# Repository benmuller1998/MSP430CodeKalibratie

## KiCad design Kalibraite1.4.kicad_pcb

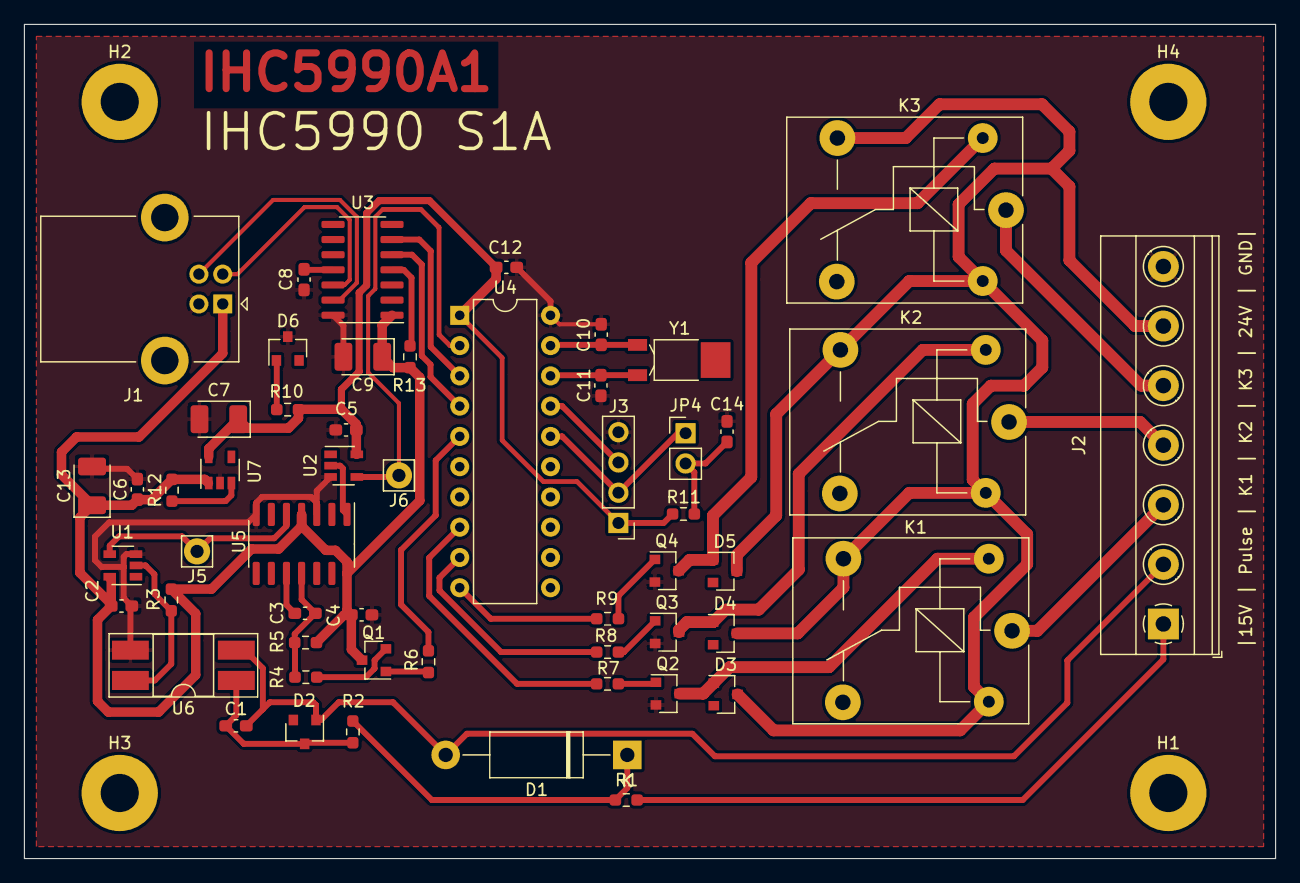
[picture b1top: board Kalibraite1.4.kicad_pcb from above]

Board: 2 copper layers, 105.0 x 70.0 mm, 58 parts (0 on the bottom side), 42 nets.

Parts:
C1: 100pF; C_0603_1608Metric_Pad1.08x0.95mm_HandSolder
C2, C4, C5, C6, C8, C12: 100nF; C_0603_1608Metric_Pad1.08x0.95mm_HandSolder
C3: 68nF; C_0603_1608Metric_Pad1.08x0.95mm_HandSolder
C7, C9, C13: 10uF; CP_EIA-3528-12_Kemet-T_Pad1.50x2.35mm_HandSolder
C10, C11: 15pF; C_0603_1608Metric_Pad1.08x0.95mm_HandSolder
C14: 10n; C_0603_1608Metric_Pad1.08x0.95mm_HandSolder
D1: P6KE13CA; D_DO-15_P15.24mm_Horizontal
D2, D3, D4, D5: 1N4148; D_SOT-23_ANK
D6: LED; D_SOT-23_ANK
H1, H2, H3, H4: MountingHole; MountingHole_3.2mm_M3_Pad
J1: USB_B; USB_B_Lumberg_2411_02_Horizontal
J2: Conn_01x07_Female; TerminalBlock_Phoenix_MKDS-1,5-7_1x07_P5.00mm_Horizontal
J3: Pin header; PinHeader_1x04_P2.54mm_Vertical
J5, J6: Header; Pin_D1.1mm_L8.5mm_W2.5mm_FlatFork
JP4: Jumper_2_Open; PinHeader_1x02_P2.54mm_Vertical
K1, K2, K3: G5LE; Relay_SPDT_SANYOU_SRD_Series_Form_C
Q1: BSN20; SOT-23
Q2, Q3, Q4: BC847; SOT-23
R1: 1K5; R_0603_1608Metric_Pad0.98x0.95mm_HandSolder
R2: 1K2; R_0603_1608Metric_Pad0.98x0.95mm_HandSolder
R3, R7, R8: 4K7; R_0603_1608Metric_Pad0.98x0.95mm_HandSolder
R4: 470; R_0603_1608Metric_Pad0.98x0.95mm_HandSolder
R5: 5K6; R_0603_1608Metric_Pad0.98x0.95mm_HandSolder
R6: 10K; R_0603_1608Metric_Pad0.98x0.95mm_HandSolder
R9, R12: 4k7; R_0603_1608Metric_Pad0.98x0.95mm_HandSolder
R10: 270; R_0603_1608Metric_Pad0.98x0.95mm_HandSolder
R11: 47k; R_0603_1608Metric_Pad0.98x0.95mm_HandSolder
R13: 1K; R_0603_1608Metric_Pad0.98x0.95mm_HandSolder
U1, U2: 74VHC1G14; SOT-23-5
U3: MCP2221AxP; SOIC-14_3.9x8.7mm_P1.27mm
U4: MSP430G2553IN20; DIP-20_W7.62mm
U5: 74121; SOIC-14_3.9x8.7mm_P1.27mm
U6: SFH617A-1; DIP-4_W8.89mm_SMDSocket_LongPads
U7: MIC5317-3.3YM5-TR; SOT-23-5
Y1: 32.768kHz; Crystal_SMD_MicroCrystal_MS1V-T1K

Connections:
+3V3: C5.1, C7.1, C12.2, J3.1, R10.1, R11.1, U2.5, U4.1, U7.5
+5V: C2.2, C4.1, C6.1, C9.1, C13.1, J1.1, Q1.3, R3.1, R5.1, R12.2, R13.2, U1.5, U3.1, U5.4, U5.14, U7.1
+24V: D3.1, D4.1, D5.1, J2.6, K1.3, K1.5, K2.3, K2.5, K3.3, K3.5
GND: C2.1, C4.2, C5.2, C6.2, C7.2, C8.1, C9.2, C10.1, C11.1, C12.1, C13.2, C14.2, D6.1, J1.4, J2.7, J3.4, Q2.2, Q3.2, Q4.2, U1.3, U2.3, U3.14, U4.20, U5.3, U5.7, U6.3, U7.2
K1: J2.3, K1.1
K2: J2.4, K2.1
K3: J2.5, K3.1
unnamed: C1.1, D2.1, R2.2, U6.1
unnamed: C1.2, D1.2, D2.2, J2.2, U6.2
unnamed: C3.1, U5.10
unnamed: C3.2, R4.2, R5.2, U5.11
unnamed: C8.2, U3.11
unnamed: C10.2, U4.19, Y1.2
unnamed: C11.2, U4.18, Y1.1
unnamed: C14.1, JP4.2, R11.2
unnamed: D1.1, R1.1, R2.1
unnamed: D3.2, K1.2, Q2.3
unnamed: D4.2, K2.2, Q3.3
unnamed: D5.2, K3.2, Q4.3
unnamed: D6.2, R10.2
unnamed: J1.2, U3.12
unnamed: J1.3, U3.13
unnamed: J2.1, R1.2
unnamed: J5.1, U1.4, U5.5
unnamed: Q1.1, R6.2
unnamed: Q1.2, R4.1
unnamed: Q2.1, R7.1
unnamed: Q3.1, R8.2
unnamed: Q4.1, R9.1
unnamed: R3.2, U1.2, U6.4
unnamed: R12.1, U7.3
unnamed: R13.1, U3.4
unnamed: U2.2, U5.1
unnamed: U3.5, U4.4
unnamed: U3.6, U4.3
P1.0: J6.1, U2.4, U4.2
P1.3: R6.1, U4.5
P2.0: R7.2, U4.8
P2.1: R8.1, U4.9
P2.2: R9.2, U4.10
RST: J3.2, JP4.1, U4.16
Test: J3.3, U4.17
